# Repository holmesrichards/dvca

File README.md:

# MFOS Dual VCA

Kosmo format version of the [Music From Outer Space Dual VCA](http://musicfromouterspace.com/analogsynth_new/DUALVCA/DLLVCA001.html) synth module.

Circuit is basically unchanged from the original except:

* Eurorack style power header added, with reversal protection diodes
* Normal connection from 1st VCA output to 2nd VCA input

## Current draw
15 mA +12 V, 15 mA -12 V

## Photos

## Documentation

* [Schematic](Docs/dualvca_schematic.pdf)
* PCB layout: [front PCB front](Docs/Layout/dualvca_FrontPCB/dualvca_FrontPCB_front.svg), [front PCB back](Docs/Layout/dualvca_FrontPCB/dualvca_FrontPCB_back.svg), [back PCB front](Docs/Layout/dualvca_BackPCB/dualvca_BackPCB_front.svg), [back PCB back](Docs/Layout/dualvca_BackPCB/dualvca_BackPCB_back.svg)
* [BOM](Docs/BOM/dualvca_bom.md)
<!-- * [Build notes](Docs/build.md) -->
<!-- * [How it works](Docs/howitworks.md) -->
<!--* [Blog post]() -->

## GitHub repository

* [https://github.com/holmesrichards/dvca](https://github.com/holmesrichards/dvca)

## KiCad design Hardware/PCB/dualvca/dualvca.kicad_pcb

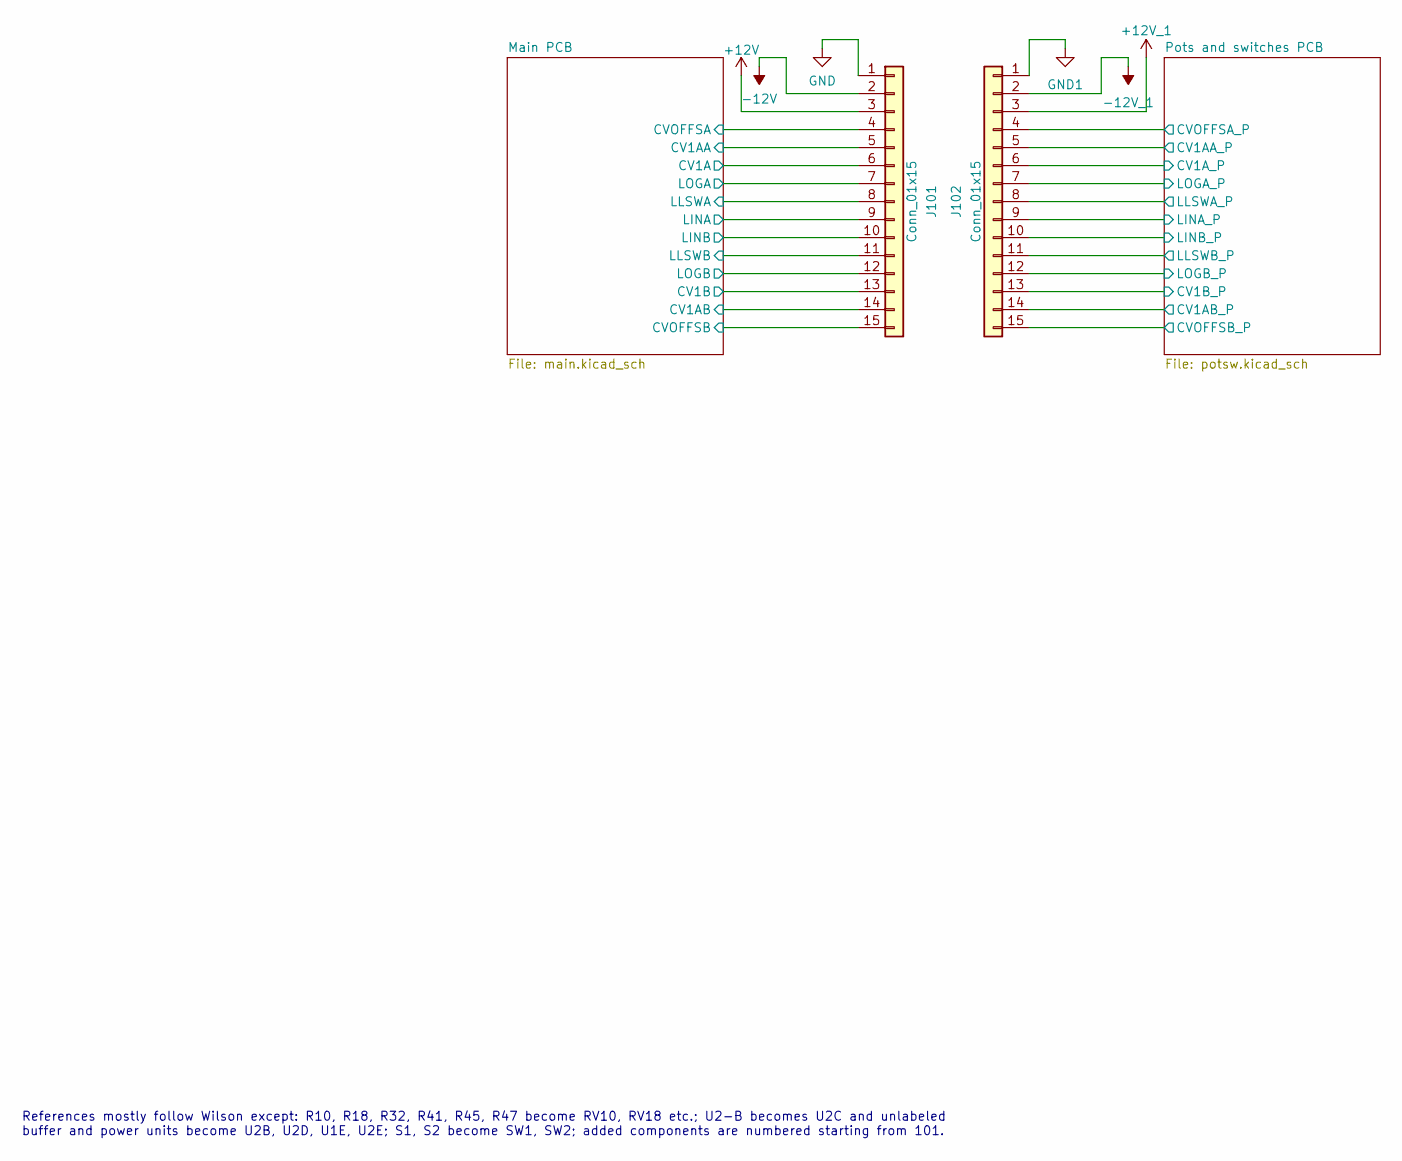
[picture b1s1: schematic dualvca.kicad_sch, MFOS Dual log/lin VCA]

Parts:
J101: Conn_01x15; PinHeader_1x15_P2.54mm_Vertical
J102: Conn_01x15; PinSocket_1x15_P2.54mm_Vertical

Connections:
+12V: J101.3; also elsewhere on the board
+12V_1: J102.3; also elsewhere on the board
-12V: J101.2; also elsewhere on the board
-12V_1: J102.2; also elsewhere on the board
/Main PCB/CV1A: J101.6; also elsewhere on the board
/Main PCB/CV1AA: J101.5; also elsewhere on the board
/Main PCB/CV1AB: J101.14; also elsewhere on the board
/Main PCB/CV1B: J101.13; also elsewhere on the board
/Main PCB/CVOFFSA: J101.4; also elsewhere on the board
/Main PCB/CVOFFSB: J101.15; also elsewhere on the board
/Main PCB/LINA: J101.9; also elsewhere on the board
/Main PCB/LINB: J101.10; also elsewhere on the board
/Main PCB/LLSWA: J101.8; also elsewhere on the board
/Main PCB/LLSWB: J101.11; also elsewhere on the board
/Main PCB/LOGA: J101.7; also elsewhere on the board
/Main PCB/LOGB: J101.12; also elsewhere on the board
/Pots and switches PCB/CV1AA_P: J102.5; also elsewhere on the board
/Pots and switches PCB/CV1AB_P: J102.14; also elsewhere on the board
/Pots and switches PCB/CV1A_P: J102.6; also elsewhere on the board
/Pots and switches PCB/CV1B_P: J102.13; also elsewhere on the board
/Pots and switches PCB/CVOFFSA_P: J102.4; also elsewhere on the board
/Pots and switches PCB/CVOFFSB_P: J102.15; also elsewhere on the board
/Pots and switches PCB/LINA_P: J102.9; also elsewhere on the board
/Pots and switches PCB/LINB_P: J102.10; also elsewhere on the board
/Pots and switches PCB/LLSWA_P: J102.8; also elsewhere on the board
/Pots and switches PCB/LLSWB_P: J102.11; also elsewhere on the board
/Pots and switches PCB/LOGA_P: J102.7; also elsewhere on the board
/Pots and switches PCB/LOGB_P: J102.12; also elsewhere on the board
GND: J101.1; also elsewhere on the board
GND1: J102.1; also elsewhere on the board

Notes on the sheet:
References mostly follow Wilson except: R10, R18, R32, R41, R45, R47 become RV10, RV18 etc.; U2-B becomes U2C and unlabeled buffer and power units become U2B, U2D, U1E, U2E; S1, S2 become SW1, SW2; added components are numbered starting from 101.

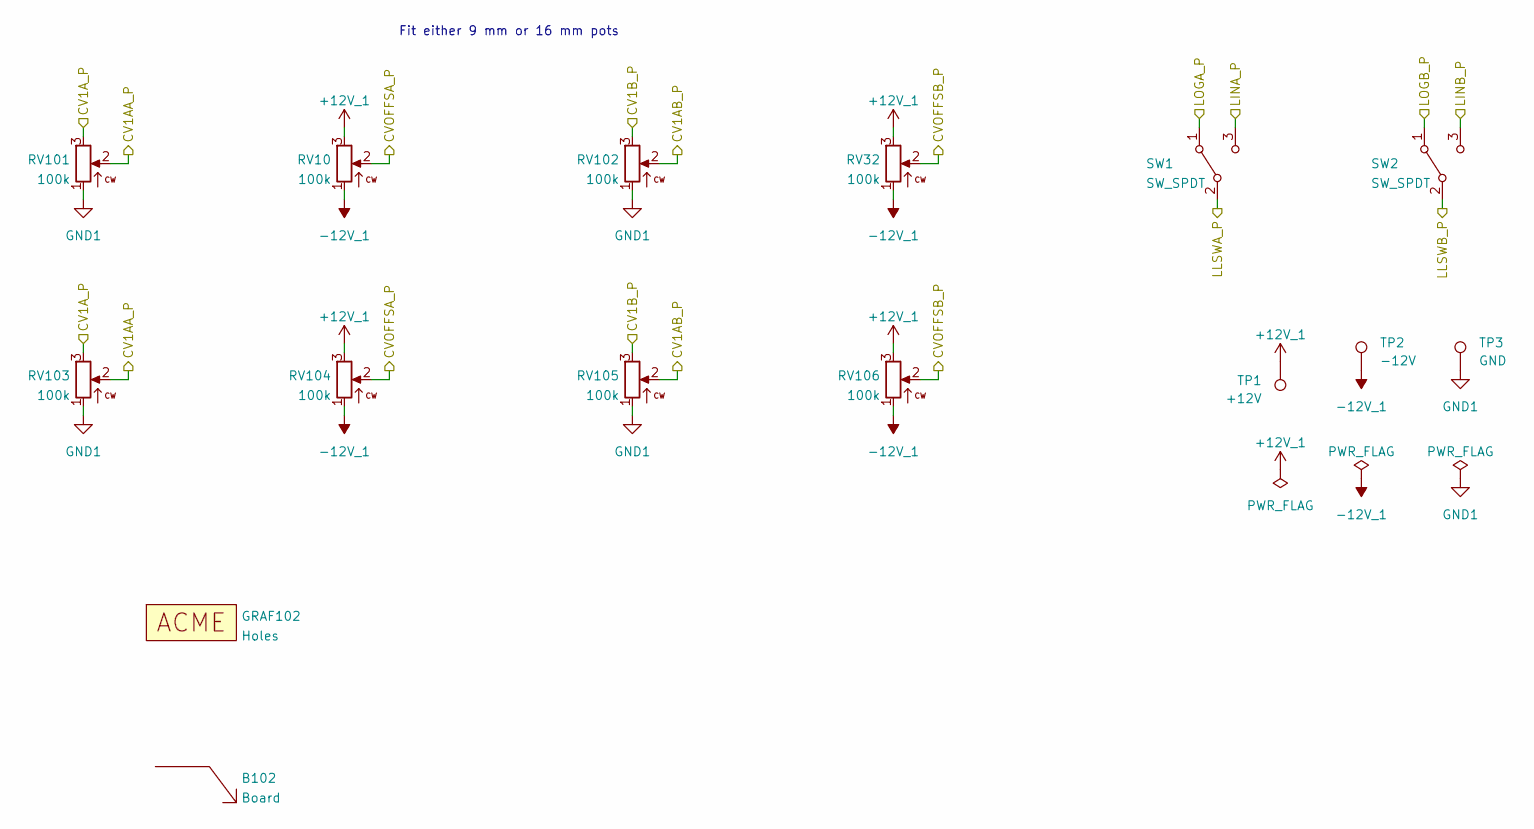
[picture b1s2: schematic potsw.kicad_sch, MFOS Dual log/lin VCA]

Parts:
B102: Board; Board_Marker
GRAF102: Holes; mfos_vca_panel_100_holes
RV10, RV32, RV101, RV102: 100k; Potentiometer_Alpha_RD901F-40-00D_Single_Vertical_centered
RV103, RV104, RV105, RV106: 100k; Potentiometer_Alpha_16mm_Single_Vertical
SW1, SW2: SW_SPDT; SPDT-toggle-switch-1M-series
TP1: +12V; TestPoint_THTPad_D1.5mm_Drill0.7mm
TP2: -12V; TestPoint_THTPad_D1.5mm_Drill0.7mm
TP3: GND; TestPoint_THTPad_D1.5mm_Drill0.7mm

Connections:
+12V_1: RV10.3, RV32.3, RV104.3, RV106.3; also elsewhere on the board
-12V_1: RV10.1, RV32.1, RV104.1, RV106.1; also elsewhere on the board
/Pots and switches PCB/CV1AA_P: RV101.2, RV103.2; also elsewhere on the board
/Pots and switches PCB/CV1AB_P: RV102.2, RV105.2; also elsewhere on the board
/Pots and switches PCB/CV1A_P: RV101.3, RV103.3; also elsewhere on the board
/Pots and switches PCB/CV1B_P: RV102.3, RV105.3; also elsewhere on the board
/Pots and switches PCB/CVOFFSA_P: RV10.2, RV104.2; also elsewhere on the board
/Pots and switches PCB/CVOFFSB_P: RV32.2, RV106.2; also elsewhere on the board
/Pots and switches PCB/LINA_P: SW1.3 (C); also elsewhere on the board
/Pots and switches PCB/LINB_P: SW2.3 (C); also elsewhere on the board
/Pots and switches PCB/LLSWA_P: SW1.2 (B); also elsewhere on the board
/Pots and switches PCB/LLSWB_P: SW2.2 (B); also elsewhere on the board
/Pots and switches PCB/LOGA_P: SW1.1 (A); also elsewhere on the board
/Pots and switches PCB/LOGB_P: SW2.1 (A); also elsewhere on the board
GND1: RV101.1, RV102.1, RV103.1, RV105.1; also elsewhere on the board

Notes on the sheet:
Fit either 9 mm or 16 mm pots

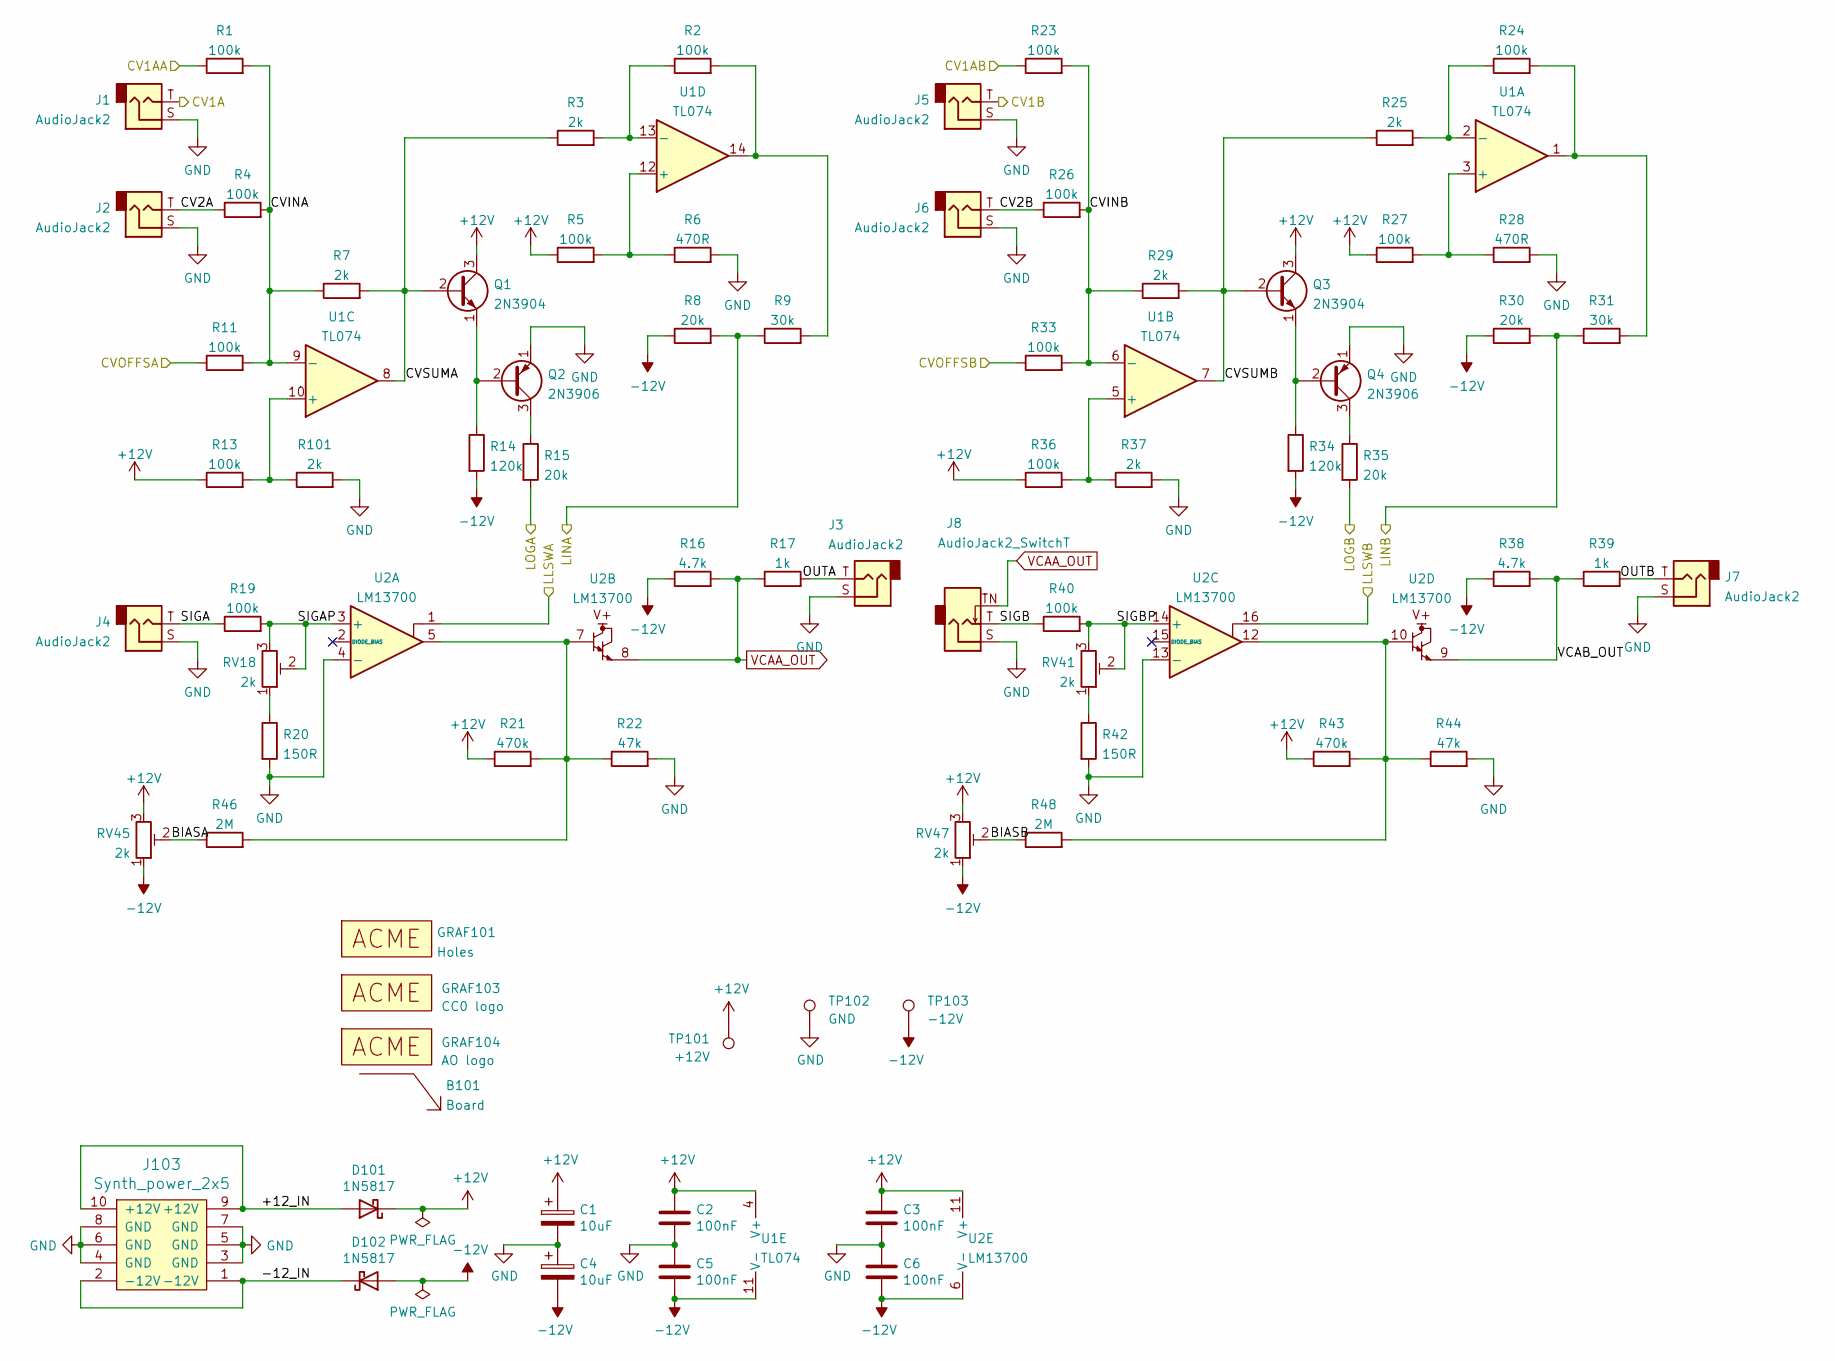
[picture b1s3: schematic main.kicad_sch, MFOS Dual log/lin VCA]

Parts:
B101: Board; Board_Marker
C1, C4: 10uF; CP_Radial_D6.3mm_P2.50mm
C2, C3, C5, C6: 100nF; C_Disc_D3.0mm_W1.6mm_P2.50mm
D101, D102: 1N5817; D_DO-41_SOD81_P10.16mm_Horizontal
GRAF101: Holes; mfos_vca_panel_100_holes
GRAF103: CC0 logo; CC0_logo
GRAF104: AO logo; analogoutput
J1, J2, J3, J4, J5, J6, J7: AudioJack2; Jack_6.35mm_PJ_629HAN_slots
J8: AudioJack2_SwitchT; Jack_6.35mm_PJ_629HAN_slots
J103: Synth_power_2x5; Power_Header
Q1, Q3: 2N3904; TO-92_Inline_Wide
Q2, Q4: 2N3906; TO-92_Inline_Wide
R1, R2, R4, R5, R11, R13, R19, R23, R24, R26, R27, R33, R36, R40: 100k; R_Axial_DIN0207_L6.3mm_D2.5mm_P10.16mm_Horizontal
R3, R7, R25, R29, R37, R101: 2k; R_Axial_DIN0207_L6.3mm_D2.5mm_P10.16mm_Horizontal
R6, R28: 470R; R_Axial_DIN0207_L6.3mm_D2.5mm_P10.16mm_Horizontal
R8, R15, R30, R35: 20k; R_Axial_DIN0207_L6.3mm_D2.5mm_P10.16mm_Horizontal
R9, R31: 30k; R_Axial_DIN0207_L6.3mm_D2.5mm_P10.16mm_Horizontal
R14, R34: 120k; R_Axial_DIN0207_L6.3mm_D2.5mm_P10.16mm_Horizontal
R16, R38: 4.7k; R_Axial_DIN0207_L6.3mm_D2.5mm_P10.16mm_Horizontal
R17, R39: 1k; R_Axial_DIN0207_L6.3mm_D2.5mm_P10.16mm_Horizontal
R20, R42: 150R; R_Axial_DIN0207_L6.3mm_D2.5mm_P10.16mm_Horizontal
R21, R43: 470k; R_Axial_DIN0207_L6.3mm_D2.5mm_P10.16mm_Horizontal
R22, R44: 47k; R_Axial_DIN0207_L6.3mm_D2.5mm_P10.16mm_Horizontal
R46, R48: 2M; R_Axial_DIN0207_L6.3mm_D2.5mm_P10.16mm_Horizontal
RV18, RV41, RV45, RV47: 2k; Potentiometer_Bourns_3296W_Vertical_standard
TP101: +12V; TestPoint_THTPad_D1.5mm_Drill0.7mm
TP102: GND; TestPoint_THTPad_D1.5mm_Drill0.7mm
TP103: -12V; TestPoint_THTPad_D1.5mm_Drill0.7mm
U1: TL074; DIP-14_W7.62mm_Socket_LongPads
U2: LM13700; DIP-16_W7.62mm_Socket_LongPads

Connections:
+12V: C1.1, C2.1, C3.1, D101.1 (K), Q1.3 (C), Q3.3 (C), R5.1, R13.1, R21.1, R27.1, R36.1, R43.1, RV45.3, RV47.3, TP101.1, U1.4 (V+), U2.11 (V+); also elsewhere on the board
-12V: C4.2, C5.2, C6.2, D102.2 (A), R8.1, R14.2, R16.1, R30.1, R34.2, R38.1, RV45.1, RV47.1, TP103.1, U1.11 (V-), U2.6 (V-); also elsewhere on the board
/Main PCB/+12_IN: D101.2 (A), J103.9 (+12V), J103.10 (+12V)
/Main PCB/-12_IN: D102.1 (K), J103.1 (-12V), J103.2 (-12V)
/Main PCB/BIASA: R46.1, RV45.2
/Main PCB/BIASB: R48.1, RV47.2
/Main PCB/CV1A: J1.T; also elsewhere on the board
/Main PCB/CV1AA: R1.1; also elsewhere on the board
/Main PCB/CV1AB: R23.1; also elsewhere on the board
/Main PCB/CV1B: J5.T; also elsewhere on the board
/Main PCB/CV2A: J2.T, R4.1
/Main PCB/CV2B: J6.T, R26.1
/Main PCB/CVINA: R1.2, R4.2, R7.1, R11.2, U1.9 (-)
/Main PCB/CVINB: R23.2, R26.2, R29.1, R33.2, U1.6 (-)
/Main PCB/CVOFFSA: R11.1; also elsewhere on the board
/Main PCB/CVOFFSB: R33.1; also elsewhere on the board
/Main PCB/CVSUMA: Q1.2 (B), R3.1, R7.2, U1.8
/Main PCB/CVSUMB: Q3.2 (B), R25.1, R29.2, U1.7
/Main PCB/LINA: R8.2, R9.1; also elsewhere on the board
/Main PCB/LINB: R30.2, R31.1; also elsewhere on the board
/Main PCB/LLSWA: U2.1; also elsewhere on the board
/Main PCB/LLSWB: U2.16; also elsewhere on the board
/Main PCB/LOGA: R15.2; also elsewhere on the board
/Main PCB/LOGB: R35.2; also elsewhere on the board
/Main PCB/OUTA: J3.T, R17.2
/Main PCB/OUTB: J7.T, R39.2
/Main PCB/SIGA: J4.T, R19.1
/Main PCB/SIGAP: R19.2, RV18.2, RV18.3, U2.3 (+)
/Main PCB/SIGB: J8.T, R40.1
/Main PCB/SIGBP: R40.2, RV41.2, RV41.3, U2.14 (+)
/Main PCB/VCAB_OUT: R38.2, R39.1, U2.9
GND: C1.2, C2.2, C3.2, C4.1, C5.1, C6.1, J1.S, J2.S, J3.S, J4.S, J5.S, J6.S, J7.S, J8.S, J103.3 (GND), J103.4 (GND), J103.5 (GND), J103.6 (GND), J103.7 (GND), J103.8 (GND), Q2.1 (E), Q4.1 (E), R6.2, R20.2, R22.2, R28.2, R37.2, R42.2, R44.2, R101.2, TP102.1, U2.4 (-), U2.13 (-); also elsewhere on the board
unnamed: Q1.1 (E), Q2.2 (B), R14.1
unnamed: Q2.3 (C), R15.1
unnamed: Q3.1 (E), Q4.2 (B), R34.1
unnamed: Q4.3 (C), R35.1
unnamed: R2.2, R9.2, U1.14
unnamed: R20.1, RV18.1
unnamed: R21.2, R22.1, R46.2, U2.5, U2.7
unnamed: R24.2, R31.2, U1.1
unnamed: R42.1, RV41.1
unnamed: R43.2, R44.1, R48.2, U2.10, U2.12
unnamed: R27.2, R28.1, U1.3 (+)
unnamed: R24.1, R25.2, U1.2 (-)
unnamed: R36.2, R37.1, U1.5 (+)
unnamed: R13.2, R101.1, U1.10 (+)
unnamed: R5.2, R6.1, U1.12 (+)
unnamed: R2.1, R3.2, U1.13 (-)
VCAA_OUT: J8.TN, R16.2, R17.1, U2.8

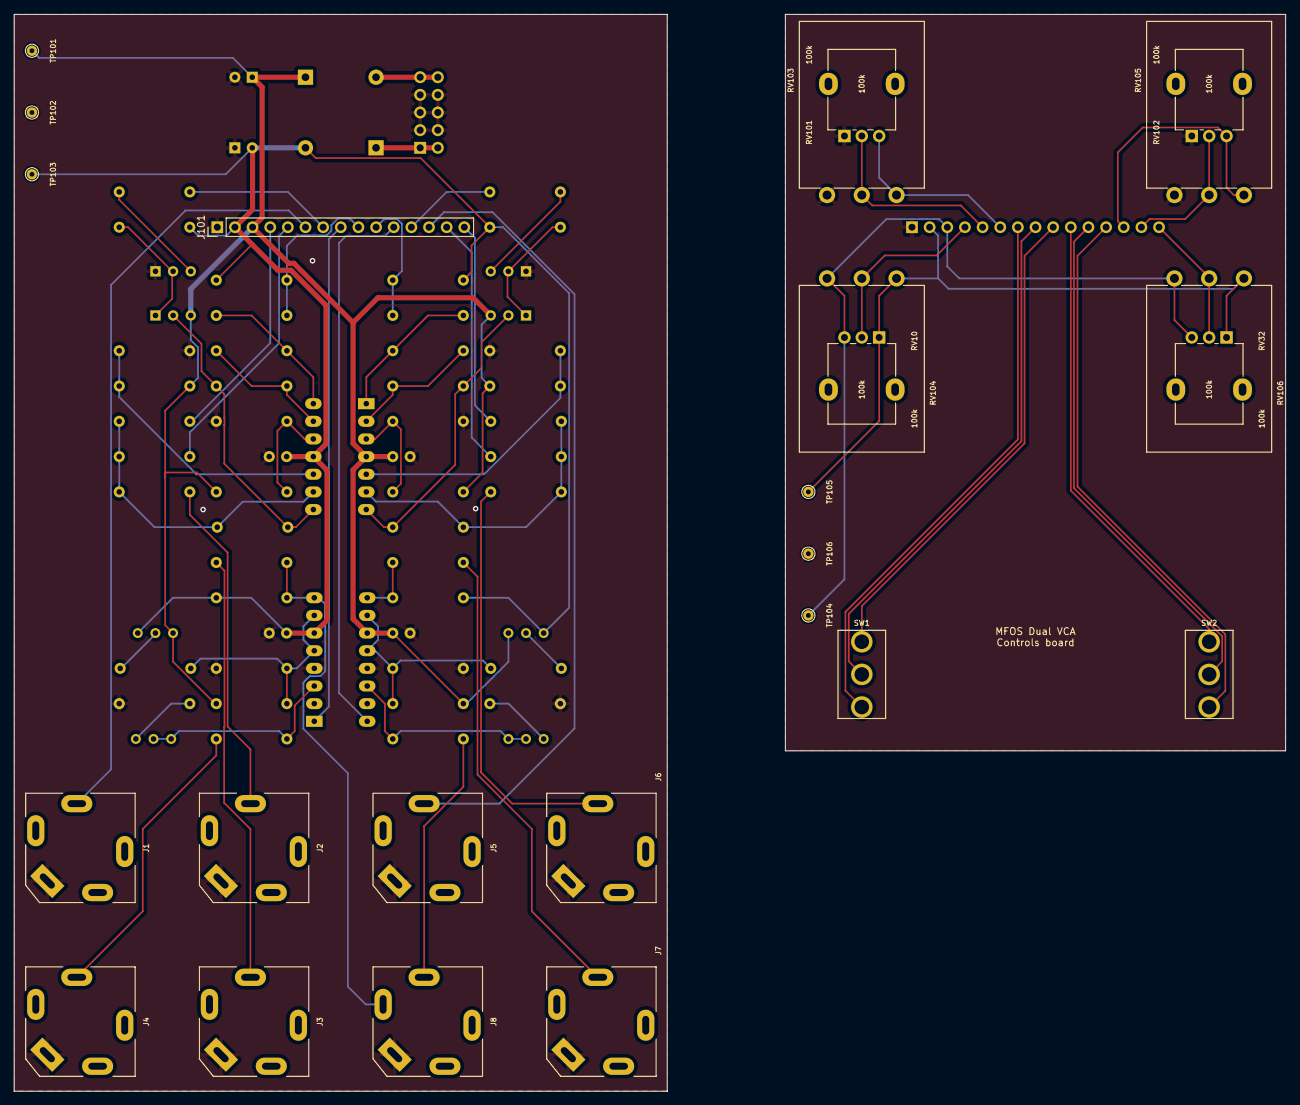
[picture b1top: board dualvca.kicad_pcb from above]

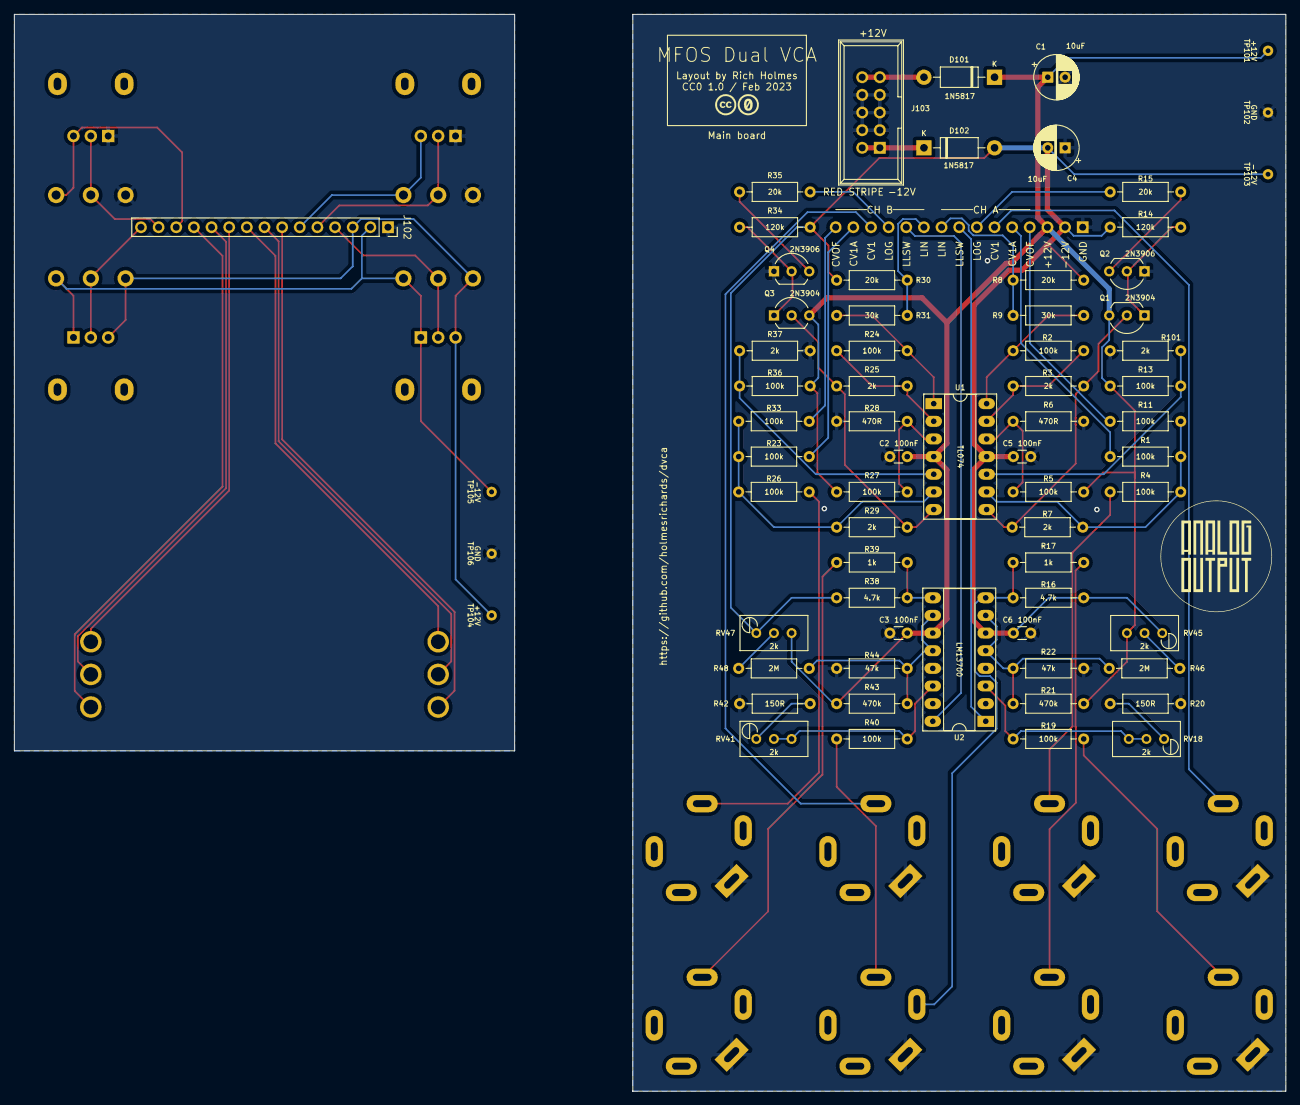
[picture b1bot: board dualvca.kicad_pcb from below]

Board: 2 copper layers, 183.0 x 155.0 mm, 93 parts (64 on the bottom side), 64 nets.

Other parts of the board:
TP104: +12V; TestPoint_THTPad_D1.5mm_Drill0.7mm
TP105: -12V; TestPoint_THTPad_D1.5mm_Drill0.7mm
TP106: GND; TestPoint_THTPad_D1.5mm_Drill0.7mm

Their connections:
+12V_1: TP104.1; also elsewhere on the board
-12V_1: TP105.1; also elsewhere on the board
GND1: TP106.1; also elsewhere on the board

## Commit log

2023-02-03 Initial version
2023-02-03 Nuke 75 mm files; better README; PDF docs
2023-02-05 KiCad 7, libraries to folder
2023-02-11 Pre fab tweaks, Gerbers
2023-02-15 Hardware, BOM
2023-02-22 gerbers
2023-02-22 libraries in new place
2023-03-13 rm libraries
2023-03-13 reorg
2023-03-14 Docs
2023-03-14 Rearrange panel labels
2023-03-17 mv 2D to Layout
2023-03-17 STEP
2023-05-17 README
